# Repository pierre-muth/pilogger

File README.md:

# pilogger
Raspberry Pi Java project to acquire, store, and display numerical data from different Channels over 5 different time scale. So far Atmospheric pressure and temperature with a BMP085 probe, Background Radiation with a serial Geiger counter, System load and memory usage of the operating system, temperature and brightness with an outside probe linked with nRF24L01+. Data are pushed online to be visualized with a google chart page :

http://muth.inc.free.fr/pilogger/index.php?scale=Day&grouped=0

Story of the project :
http://pierremuth.wordpress.com/rpiadventure/

Linked with this hardware project :
https://code.google.com/p/dvi-el-display/

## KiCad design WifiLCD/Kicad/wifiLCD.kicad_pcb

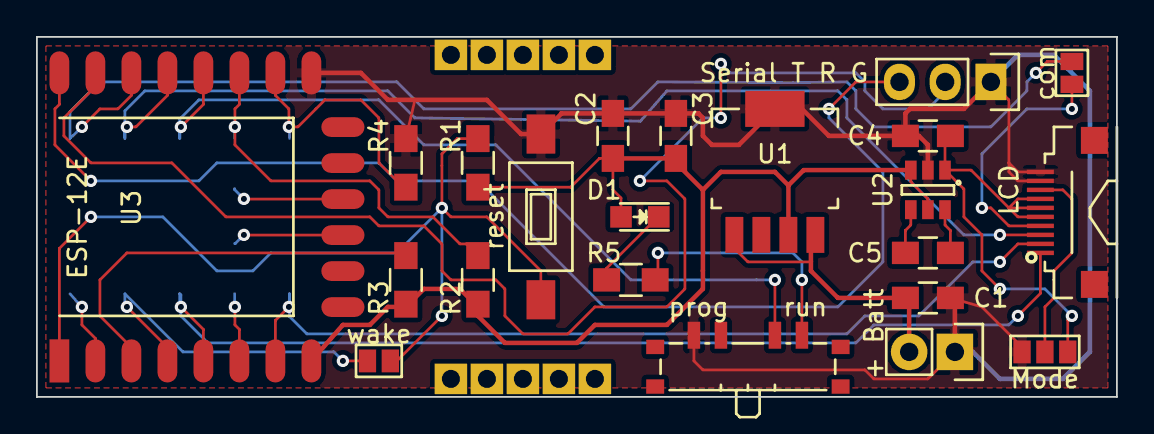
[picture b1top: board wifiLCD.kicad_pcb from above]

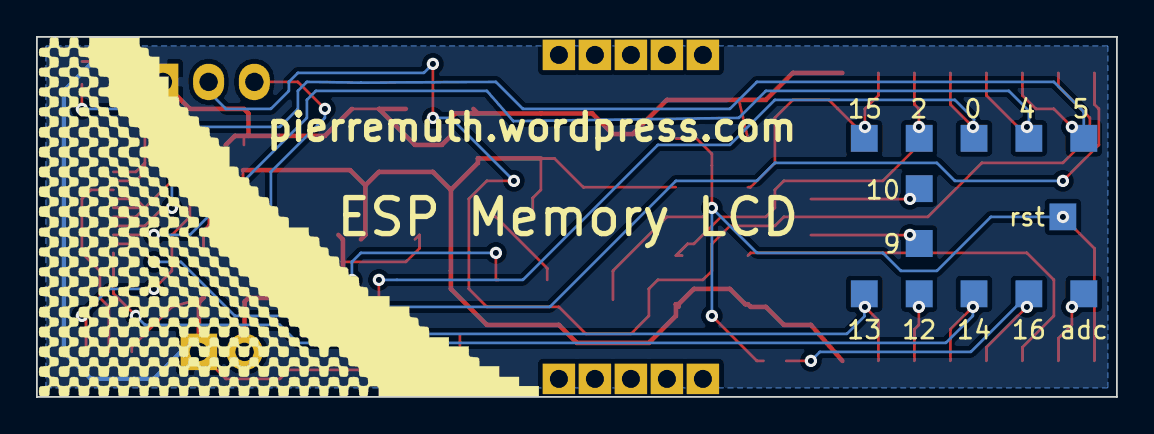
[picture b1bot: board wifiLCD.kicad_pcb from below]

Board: 2 copper layers, 60.0 x 20.0 mm, 35 parts (13 on the bottom side), 26 nets.

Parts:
0: G0; Measurement_Point_Square-SMD-Pad_Small
2: G2; Measurement_Point_Square-SMD-Pad_Small
4: G4; Measurement_Point_Square-SMD-Pad_Small
5: G5; Measurement_Point_Square-SMD-Pad_Small
9: G9; Measurement_Point_Square-SMD-Pad_Small
10: G10; Measurement_Point_Square-SMD-Pad_Small
12: G12; Measurement_Point_Square-SMD-Pad_Small
13: G13; Measurement_Point_Square-SMD-Pad_Small
14: G14; Measurement_Point_Square-SMD-Pad_Small
15: G15; Measurement_Point_Square-SMD-Pad_Small
16: G16; Measurement_Point_Square-SMD-Pad_Small
+ Batt: + Batt; Socket_Strip_Straight_1x02
C1, C2, C4: 2.2uF; C_0805_HandSoldering
C3: 1uF; C_0805_HandSoldering
C5: 0.22uF; C_0805_HandSoldering
D1: Red; LED_0805
LCD: Sharp_Memory_LCD; 10pins_0.5mm_PITCH_connector_FPC
Mode: Mode; GS3
R1, R2, R3, R4: 10K; R_0805_HandSoldering
R5: 1K; R_0805_HandSoldering
Serial T R G: Serial T R G; Socket_Strip_Straight_1x03
U1: LP38692; SOT-223-5
U2: REG710; SOT-23-6
U3: ESP-12E
adc: ADC; Measurement_Point_Square-SMD-Pad_Small
com: com; GS2
prog    run: prog run; Switch_SP3T
reset: Reset; SW_SPST_FSMSM
rst: RST; Measurement_Point_Square-SMD-Pad_Small
wake: wake; GS2

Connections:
+3V3: C2.1, C3.1, D1.2, R1.1, R2.1, R3.1, U1.3, U2.3, U2.5, U3.8
+5V: C4.1, LCD.5, LCD.6, LCD.7, Mode.3, U2.1
+BATT: + Batt.2, C1.1, U1.1, U1.4
/CH_PD: R3.2, U3.3
/GPIO0: 0.1, U3.18, prog run.3
/GPIO2: 2.1, R2.2, U3.17
/GPIO4: 4.1, LCD.3, U3.19
/GPIO5: 5.1, U3.20, com.1
/GPIO15: 15.1, R4.1, U3.16
/MODECOM: LCD.8, Mode.2
/RST: R1.2, U3.1, reset.1, rst.1, wake.2
GND: + Batt.1, C1.2, C2.2, C3.2, C4.2, LCD.9, LCD.10, Mode.1, R4.2, Serial T R G.1, U1.5, U2.2, U3.15, prog run.1, reset.2
unnamed: C5.1, U2.6
unnamed: C5.2, U2.4
unnamed: D1.1, R5.1
unnamed: 16.1, U3.4, wake.1
unnamed: LCD.4, com.2
unnamed: Serial T R G.2, U3.21
unnamed: Serial T R G.3, U3.22
unnamed: 14.1, LCD.1, U3.5
unnamed: 13.1, LCD.2, U3.7
unnamed: R5.2, prog run.4
unnamed: U3.2, adc.1
unnamed: 12.1, U3.6
unnamed: 9.1, U3.11
unnamed: 10.1, U3.12

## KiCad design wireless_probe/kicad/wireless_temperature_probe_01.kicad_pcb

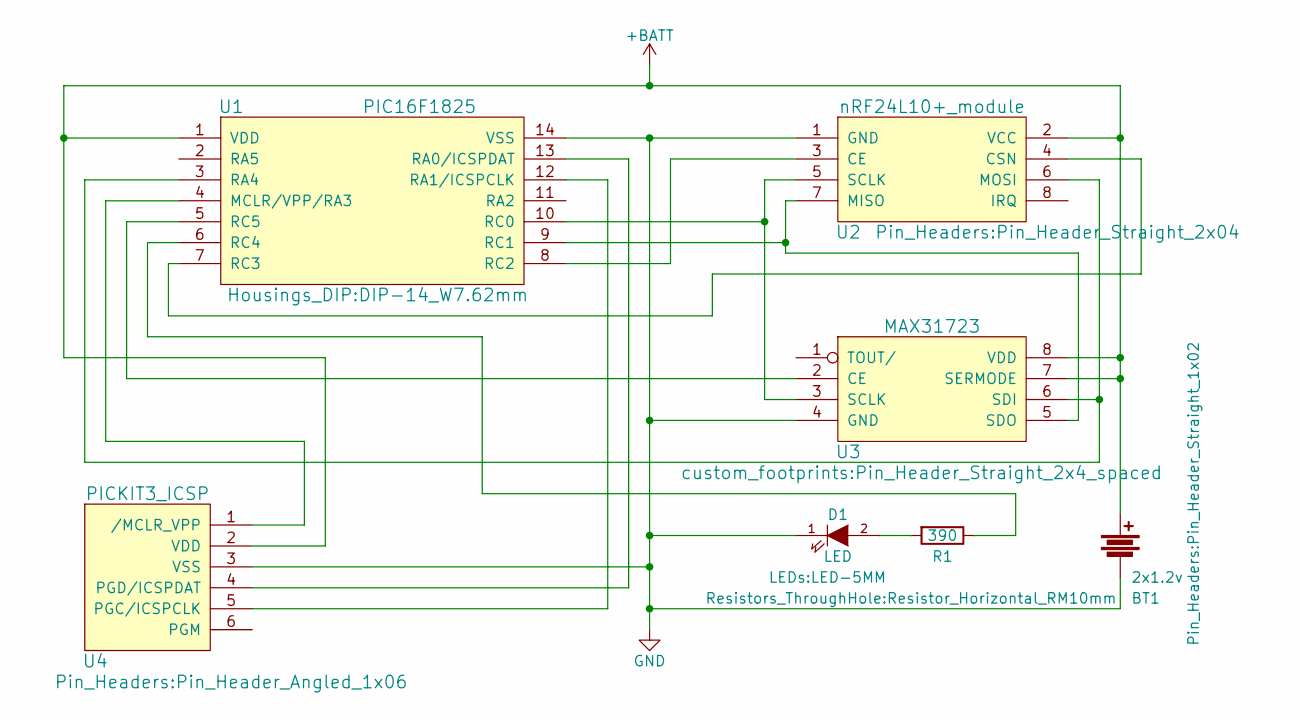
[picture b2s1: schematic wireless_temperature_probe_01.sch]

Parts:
BT1: 2x1.2v; Pin_Header_Straight_1x02
D1: LED; LED-5MM
R1: 390; Resistor_Horizontal_RM10mm
U1: PIC16F1825; DIP-14_W7.62mm
U2: nRF24L10+_module; Pin_Header_Straight_2x04
U3: MAX31723; Pin_Header_Straight_2x4_spaced
U4: PICKIT3_ICSP; Pin_Header_Angled_1x06

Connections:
+BATT: BT1.1, U1.1 (VDD), U2.2 (VCC), U3.7 (SERMODE), U3.8 (VDD), U4.2 (VDD)
GND: BT1.2, D1.1 (K), U1.14 (VSS), U2.1 (GND), U3.4 (GND), U4.3 (VSS)
unnamed: D1.2 (A), R1.2
unnamed: R1.1, U1.6 (RC4)
unnamed: U1.3 (RA4), U2.6 (MOSI), U3.6 (SDI)
unnamed: U1.4 (MCLR/VPP/RA3), U4.1 (/MCLR_VPP)
unnamed: U1.5 (RC5), U3.2 (CE)
unnamed: U1.7 (RC3), U2.4 (CSN)
unnamed: U1.8 (RC2), U2.3 (CE)
unnamed: U1.9 (RC1), U2.7 (MISO), U3.5 (SDO)
unnamed: U1.10 (RC0), U2.5 (SCLK), U3.3 (SCLK)
unnamed: U1.12 (RA1/ICSPCLK), U4.5 (PGC/ICSPCLK)
unnamed: U1.13 (RA0/ICSPDAT), U4.4 (PGD/ICSPDAT)

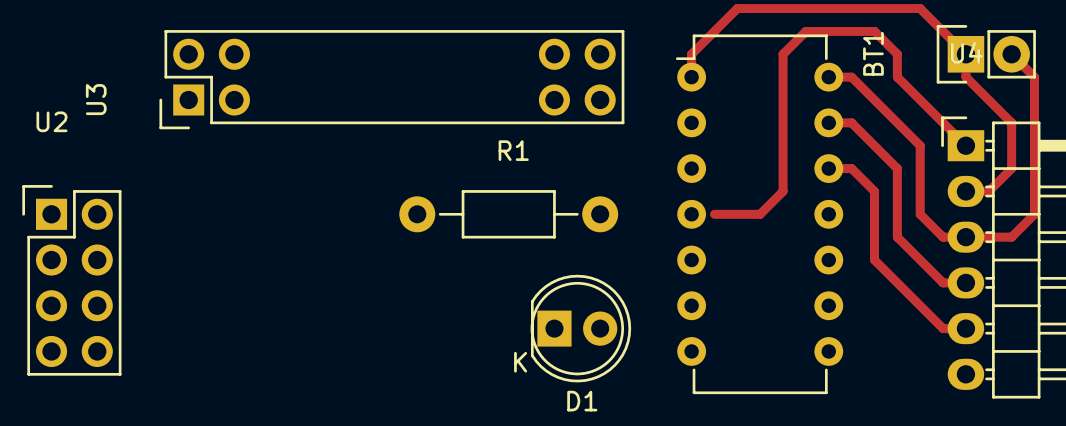
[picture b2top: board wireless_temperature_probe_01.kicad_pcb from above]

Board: 2 copper layers, 7 parts (0 on the bottom side), 13 nets.

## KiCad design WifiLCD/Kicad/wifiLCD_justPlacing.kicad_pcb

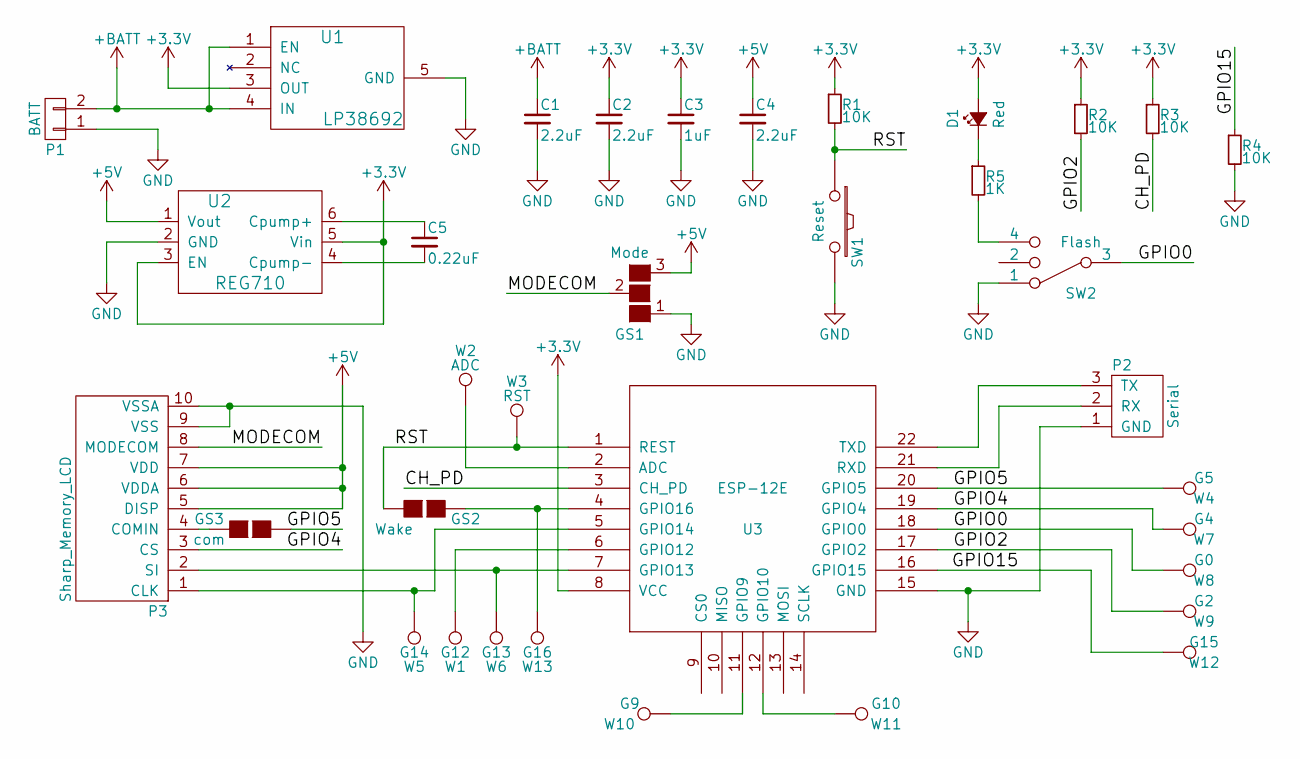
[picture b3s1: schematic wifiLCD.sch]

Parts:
C1, C2, C4: 2.2uF; C_0805_HandSoldering
C3: 1uF; C_0805_HandSoldering
C5: 0.22uF; C_0805_HandSoldering
D1: Red; LED_0805
GS1: Mode; GS3
GS2: Wake; GS2
GS3: com; GS2
P1: BATT; PINHEAD1-2
P2: Serial; Socket_Strip_Straight_1x03
P3: Sharp_Memory_LCD; 10pins_0.5mm_PITCH_connector_FPC
R1, R2, R3, R4: 10K; R_0805_HandSoldering
R5: 1K; R_0805_HandSoldering
SW1: Reset; SW_SPST_FSMSM
SW2: Flash; SW_SP3T_PCM13
U1: LP38692; SOT-223-5
U2: REG710; SOT-23-6
U3: ESP-12E
W1: G12; Measurement_Point_Square-SMD-Pad_Big
W2: ADC; Measurement_Point_Square-SMD-Pad_Big
W3: RST; Measurement_Point_Square-SMD-Pad_Big
W4: G5; Measurement_Point_Square-SMD-Pad_Big
W5: G14; Measurement_Point_Square-SMD-Pad_Big
W6: G13; Measurement_Point_Square-SMD-Pad_Big
W7: G4; Measurement_Point_Square-SMD-Pad_Big
W8: G0; Measurement_Point_Square-SMD-Pad_Big
W9: G2; Measurement_Point_Square-SMD-Pad_Big
W10: G9; Measurement_Point_Square-SMD-Pad_Big
W11: G10; Measurement_Point_Square-SMD-Pad_Big
W12: G15; Measurement_Point_Square-SMD-Pad_Big
W13: G16; Measurement_Point_Square-SMD-Pad_Big

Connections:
+3V3: C2.1, C3.1, D1.2 (A), R1.1, R2.1, R3.1, U1.3 (OUT), U2.3 (EN), U2.5 (Vin), U3.8 (VCC)
+5V: C4.1, GS1.3 (G3), P3.5 (DISP), P3.6 (VDDA), P3.7 (VDD), U2.1 (Vout)
+BATT: C1.1, P1.2, U1.1 (EN), U1.4 (IN)
/CH_PD: R3.2, U3.3 (CH_PD)
/GPIO0: SW2.3, U3.18 (GPIO0), W8.1
/GPIO2: R2.2, U3.17 (GPIO2), W9.1
/GPIO4: P3.3 (CS), U3.19 (GPIO4), W7.1
/GPIO5: GS3.1 (G1), U3.20 (GPIO5), W4.1
/GPIO15: R4.1, U3.16 (GPIO15), W12.1
/MODECOM: GS1.2 (G2), P3.8 (MODECOM)
/RST: GS2.2 (G2), R1.2, SW1.1, U3.1 (REST), W3.1
GND: C1.2, C2.2, C3.2, C4.2, GS1.1 (G1), P1.1, P2.1 (GND), P3.9 (VSS), P3.10 (VSSA), R4.2, SW1.2, SW2.1, U1.5 (GND), U2.2 (GND), U3.15 (GND)
unnamed: C5.1, U2.6 (Cpump+)
unnamed: C5.2, U2.4 (Cpump-)
unnamed: D1.1 (K), R5.1
unnamed: GS2.1 (G1), U3.4 (GPIO16), W13.1
unnamed: GS3.2 (G2), P3.4 (COMIN)
unnamed: P2.2 (RX), U3.21 (RXD)
unnamed: P2.3 (TX), U3.22 (TXD)
unnamed: P3.1 (CLK), U3.5 (GPIO14), W5.1
unnamed: P3.2 (SI), U3.7 (GPIO13), W6.1
unnamed: R5.2, SW2.4
unnamed: U3.2 (ADC), W2.1
unnamed: U3.6 (GPIO12), W1.1
unnamed: U3.11 (GPIO9), W10.1
unnamed: U3.12 (GPIO10), W11.1

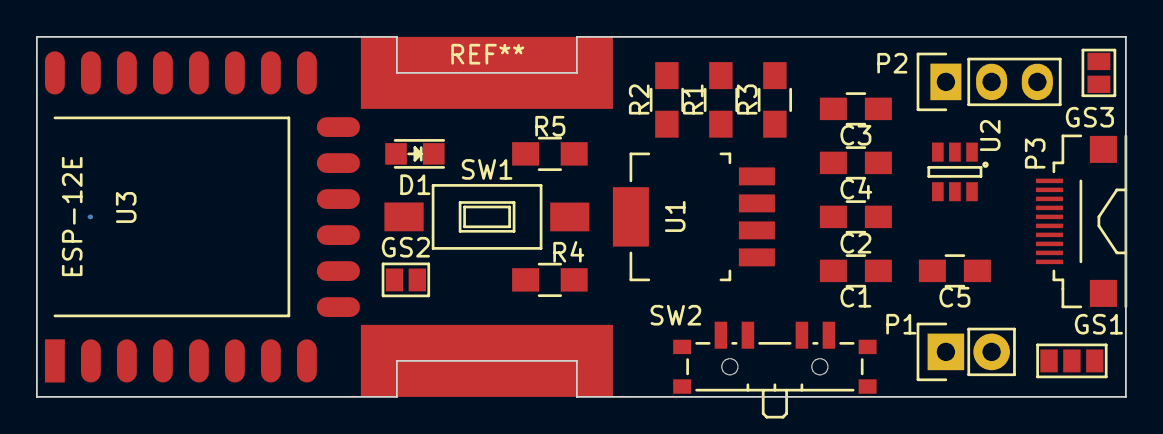
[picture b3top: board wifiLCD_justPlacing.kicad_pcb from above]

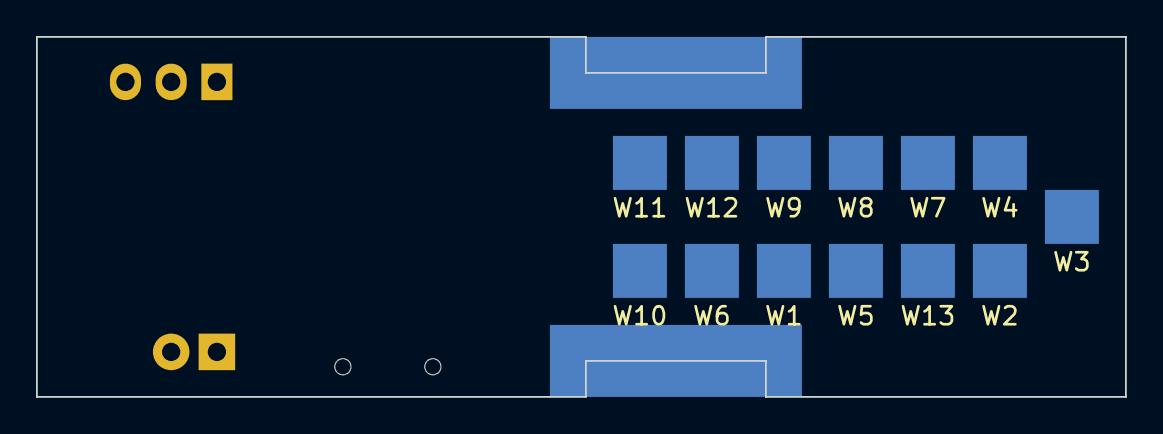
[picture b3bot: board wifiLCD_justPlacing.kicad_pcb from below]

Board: 2 copper layers, 60.5 x 20.0 mm, 35 parts (13 on the bottom side), 26 nets.

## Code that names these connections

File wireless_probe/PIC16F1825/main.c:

/* 
 * File:   main.c
 * Author: pfreyerm
 *
 * Created on November 27, 2014, 3:23 PM
 */
#include <xc.h>         /* XC8 General Include File */
#include <stdio.h>
#include <stdlib.h>

#pragma config FOSC = INTOSC    // Oscillator Selection (INTOSC oscillator: I/O function on CLKIN pin)
#pragma config WDTE = SWDTEN    // Watchdog Timer Enable by soft
#pragma config MCLRE = OFF      // MCLR Pin Function Select 
#pragma config BOREN = OFF      // Brown-out Reset Enable (Brown-out Reset disabled)
#pragma config PLLEN = OFF      // PLL Enable (4x PLL disabled)
  
#define _XTAL_FREQ  (8000000UL)

// nRF commands
#define W_TX_PAYLOAD    0b10100000
#define W_CONFIG        0b00100000
#define R_CONFIG        0b00000000
#define W_TX_ADDR       0b00110000
#define W_SETUP_RETR    0b00100100
#define W_RF_SETUP      0b00100110
#define W_SATUS         0b00100111
#define R_SATUS         0b00000111
#define FLUSH_TX        0b11100001
#define W_FEATURE       0b00111101
#define W_DYNPD         0b00111100

//MAX312723 cmmands
#define W_CONFIG_MAX    0x80

// nFR24L01 control pins
#define CE_nRF  RC2
#define CSN_nRF RC3
#define CE_TempProbe  RC5

// solar brightness
#define Solar_Pin = RA2

// Pins
#define LED RC4

//proto
void nRF_spiRW(char command, char * data, int dataLength);
void tempProbe_spiRW(char command, char* data, int dataLength);
void sendData();

//global var
unsigned char payload[32];        //Payload for nRF24L01+
unsigned char result[8];

  
void main() {
    OSCCONbits.IRCF = 0b1110;   // 8MHz
    WDTCONbits.WDTPS = 0b01100; // watchdog for 4sec sleep

    ANSELC = 0b00000000;    // no analog on port C
    ANSELA = 0b00000100;    // A2 analog input

    TRISC4 = 0;             // LED output
    TRISC2 = 0;             // SPI nFR CE command pin
    TRISC3 = 0;             // SPI nFR CSN command pin
    TRISC5 = 0;             // SPI MAX CE command pin
    TRISC0 = 0;             // SPI CLK as output
    TRISC1 = 1;             // SPI SDI as input

    TRISA4 = 0;             // SPI SDO as output
    TRISA2 = 1;             // analog Solar input

    SDOSEL = 1;             // SPI SDO on pin4: RA4
    SSSEL = 1;              // SS1 on RA3
    CKP = 1;                // SPI clk phase
    CKE = 0;                // SPI clk default low
    SSPM0 = 0;              // SPI clock Fosc/64
    SSPM1 = 1;              // "
    SSPM2 = 0;              // "
    SSPM3 = 0;              // "
    SSPEN = 1;              // Enable SPI

    unsigned char i = 0;

    CSN_nRF = 1;
    CE_TempProbe = 0;

    __delay_ms(1);
    // configure TempProbe for 1 shot conversion
    payload[0] = 0b00010111;
    tempProbe_spiRW(0x80, payload, 1);

    while(1){
        // start voltage reference
        FVRCONbits.ADFVR = 0b01;    // Internal 1.024v ref
        FVRCONbits.FVREN = 1;                  // Enable FVR module

        // Get temperature and relaunch measurement
        payload[0] = 0b00000000;
        tempProbe_spiRW(0x01, payload, 1); // read temp LSB
        result[0] = payload[0];
        payload[0] = 0b00000000;
        tempProbe_spiRW(0x02, payload, 1); // read temp MSB
        result[1] = payload[0];
        payload[0] = 0b00010111;
        tempProbe_spiRW(0x80, payload, 1); // configure TempProbe for 1 shot conversion

        // get battery voltage
        while(!FVRCONbits.FVRRDY) {}; // Wait for FVR to be stable
        ADCON1bits.ADFM = 1;        // Right justify result
        ADCON0bits.CHS = 0b11111;   // FVR is ADC input
        ADCON1bits.ADPREF = 0b00;   // Positive ref is Vdd (default)
        ADCON1bits.ADNREF = 0b00;   // Negative ref is GND (default)
        ADCON1bits.ADCS = 0b010;     // 4us conversion
        ADCON0bits.ADON = 1;        // Turn on ADC module

        __delay_us(20);
        ADCON0bits.GO_nDONE = 1;    // Start a conversion
        while (ADCON0bits.GO_nDONE) {} ;// Wait for it to be completed

        result[2] = ADRESH;         // Store the result in adc_val
        result[3] = ADRESL;

//        // get brighness
//        ADCON0bits.CHS = 0b00010;   // A2 is ADC input
//        ADCON1bits.ADPREF = 0b11;   // Positive ref is FVR
//        ADCON1bits.ADNREF = 0b00;   // Negative ref is GND (default)
//
//        __delay_us(20);
//        ADCON0bits.GO_nDONE = 1;    // Start a conversion
//        while (ADCON0bits.GO_nDONE) {} ;// Wait for it to be completed
//
//        result[4] = ADRESH;         // Store the result in adc_val
//        result[5] = ADRESL;

        // adc, fvr off
        FVREN = 0;                  // disable FVR module
        ADCON0bits.ADON = 0;        // disable ADC

        LED = 1;
        sendData();
        LED = 0;

        // watch dog enable to wake-up after 4sec
        SWDTEN = 1;
        SLEEP();
        NOP();
    }
}

void tempProbe_spiRW(char command, char * data, int dataLength){
    CKP = 1;                // SPI clk phase
    CKE = 0;                // SPI clk default low

    CE_TempProbe = 1;
    SSPBUF = command;
    while (BF == 0){;}
    TXREG = SSPBUF;
    while (TRMT == 0){;}

    for(unsigned int i=0; i<dataLength; i++){
        SSPBUF = data[i];
        while (BF == 0){;}
        data[i] = SSPBUF;
        TXREG = data[i];
        while (TRMT == 0){;}
    }
    CE_TempProbe = 0;
}

void nRF_spiRW(char command, char * data, int dataLength){
    CKP = 0;                // SPI clk phase
    CKE = 1;                // SPI clk default low

    CSN_nRF = 0;
    SSPBUF = command;
    while (BF == 0){;}
    TXREG = SSPBUF;
    while (TRMT == 0){;}

    for(unsigned int i=0; i<dataLength; i++){
        SSPBUF = data[i];
        while (BF == 0){;}
        data[i] = SSPBUF;
        TXREG = data[i];
        while (TRMT == 0){;}
    }
    CSN_nRF = 1;
}

void sendData(){
    // nFR24L01+ re-init
    payload[0] = 0b00001110;
    nRF_spiRW(W_CONFIG, payload, 1);  // Power up
    __delay_ms(5);

    payload[0] = 0b00000100;
    nRF_spiRW(W_FEATURE, payload, 1);  // write FEATURE enable dynamic payload

    payload[0] = 0b00111111;
    nRF_spiRW(W_DYNPD, payload, 1);  // enable dynamic payload for all pipes

    payload[0] = 0xC5;
    payload[1] = 0xC2;
    payload[2] = 0xC2;
    payload[3] = 0xC2;
    payload[4] = 0xC2;
    nRF_spiRW(W_TX_ADDR, payload, 5);  // TX address

    payload[0] = 0b00100110;
    nRF_spiRW(W_RF_SETUP, payload, 1);  // 250Kbps

    payload[0] = 0b00011111;
    nRF_spiRW(W_SETUP_RETR, payload, 1);  // retransmit up to 15 times every 500us

    payload[0] = 0b01111110;
    nRF_spiRW(W_SATUS, payload, 1);  // clear MAX_TR flag

    nRF_spiRW(FLUSH_TX, payload, 0);       // Flush TX fifo

    // Send over the air
    payload[0] = 'T';
    payload[1] = '2';
    payload[2] = result[0];
    payload[3] = result[1];
    payload[4] = 'B';
    payload[5] = '2';
    payload[6] = result[2];
    payload[7] = result[3];
//    payload[8] = 'L';
//    payload[9] = '2';
//    payload[10] = result[4];
//    payload[11] = result[5];

    nRF_spiRW(W_TX_PAYLOAD, payload, 8);

    // sending signal
    CE_nRF = 1;
    __delay_us(50);
    CE_nRF = 0;
    __delay_ms(1);
    payload[0] = 0b00001100;
    nRF_spiRW(W_CONFIG, payload, 1);  // Power down
    __delay_ms(1);

}

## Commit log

2013-08-12 Initial directory structure.
2013-08-15 Initial import.
2013-09-13 adding hour time scale adding min max area on chart start in full-screen
2013-09-13 First step on saving log file
2013-09-15 Save and load log files, one per channel
2013-09-16 Add fileName in constructor of a Channel for log file naming
2013-09-17 Add system Probe
2013-09-17 problems with pi4j get CPU temp
2013-09-18 font and color adjustements
2013-09-22 start test with nFR24L01+
2013-09-23 work on nRF24L01+
2013-09-24 added a first version of wireless probe
2013-09-25 In wireless probe, some byte are unsigned
2013-09-25 correct some bug in DS18B20 decoding but remain to handle negative temperature values
2013-09-29 handle correctly negative values of BMP085 start FTP uploading
2013-09-29 some minor bugs
2013-10-01 Upload Day and month data to FTP
2013-10-07 bugs
2013-10-31 Created wiki page through web user interface.
2013-10-31 Edited wiki page PageName through web user interface.
2013-10-31 Deleted wiki page PageName through web user interface.
2014-01-17 add config component support
2014-01-19 Added Watchdog to reset nFR24L01 if no interrupt recieved after timeout (20s).
2014-01-19 Added blink panels to shows data comming
2014-01-28 Change loading process
2014-02-22 Add humidity DHT03 channel on wireless probe
2014-03-20 Change file handling
2014-03-22 Add CPU temp channel Channels led are clickable to enable/disable recording, realtime chart is always valid Change a bit data rate of system probe and BMP085
2014-04-03 re-organizing start imp of Magnetometer HMC5983 Probe
2014-04-03 change ftp uploading
2014-04-03 add differential channel option
2014-04-07 remove events
2014-04-07 refactoring add a button to reload log file per channel remove dataChannel events
2014-04-27 Changing ftp upload strategy
2014-05-08 Add magnetometer HMC5983 probe reduce points on charts to reduce system load
2014-05-11 Small changes on probes and gui
2014-05-11 add test
2014-10-13 logo
2014-10-14 Add Inst. power Consumption channel to wireless probe.
2014-11-08 small changes on channel, temp
2014-11-11 remove adding point in log when not new data arrived
2014-11-11 check if not directory
2014-11-24 Edited wiki page PowerConsumptionPICcode through web user interface.
2015-03-18 Migrating wiki contents from Google Code
2015-12-20 Update with life-time scale Adding another temperature channel on nRF24l01 probes
2015-12-20 Adding source and schematics of wireless probe base on PIC16F1825, nRF24L01 and MAX312723.
2015-12-21 put GNU license
2016-06-21 Add mailbox wireless probe
2016-08-02 Prepare remote wifi LCD screen
2016-08-02 First prototype of Wifi LCD
    ESP8266 running NodeMCU LUA
2016-12-03 Add .hex file for mailbox PIC16F1825 probe
2017-07-06 Refactoring 01 WiFi display update
2017-11-06 branch for AD monitor
